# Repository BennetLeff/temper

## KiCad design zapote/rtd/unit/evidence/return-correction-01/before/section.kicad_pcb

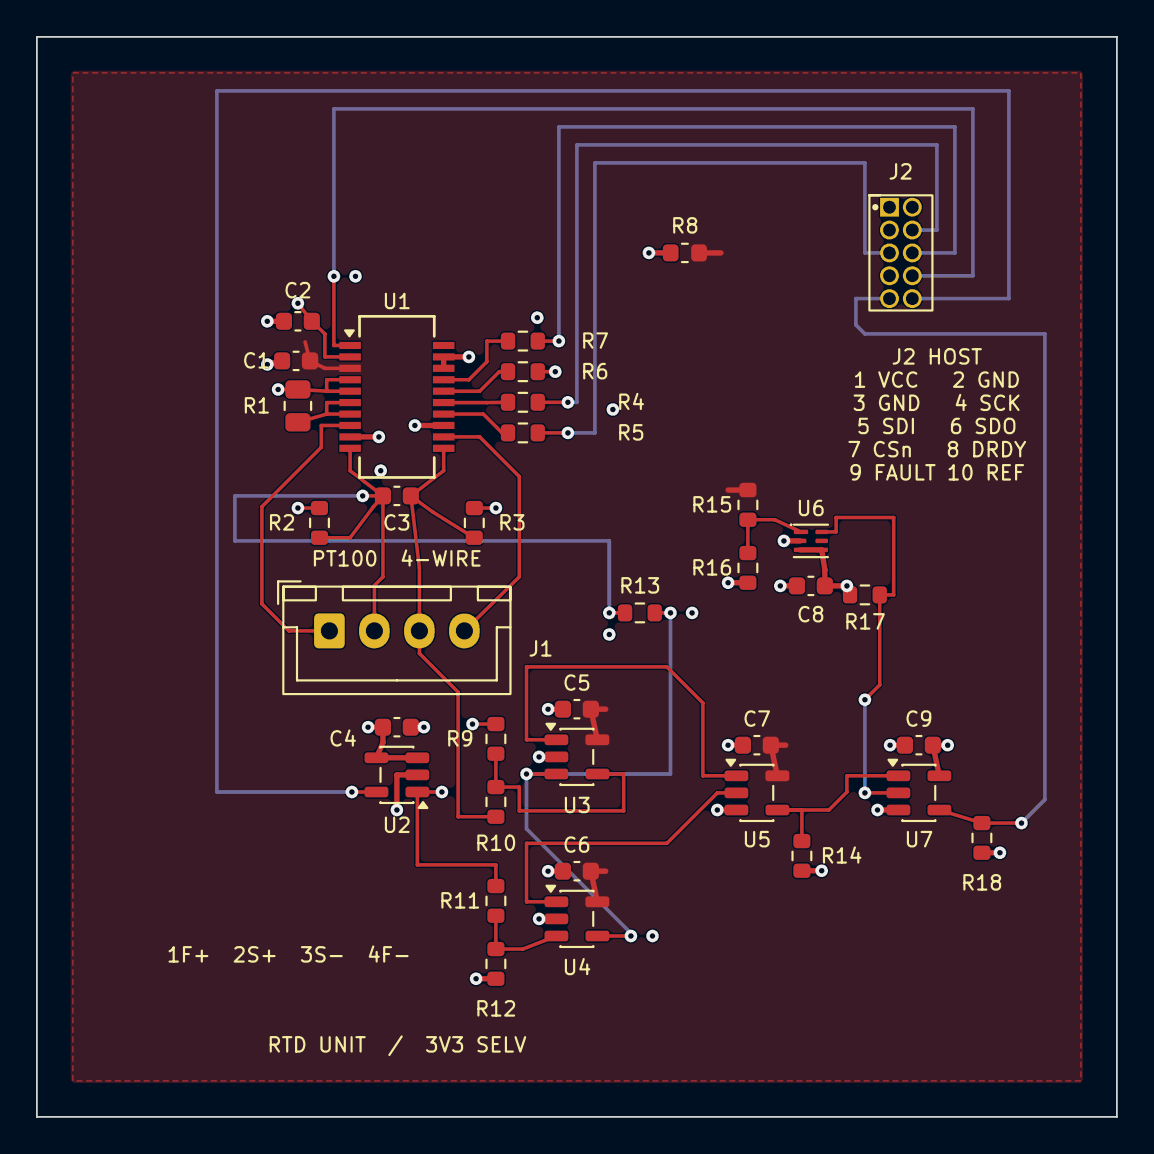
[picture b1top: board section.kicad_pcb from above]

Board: 4 copper layers, 60.0 x 60.0 mm, 36 parts (0 on the bottom side), 29 nets.

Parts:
C1, C2, C4, C5, C6, C7, C8, C9: C0603C104K5RACTU; C_0603_1608Metric
C3: C0603C102J5GACTU; C_0603_1608Metric
J1: B4B-XH-A(LF)(SN); JST_XH_B4B-XH-A_1x04_P2.50mm_Vertical
J2: FTSH-105-01-F-D; FTSH-105-01-F-D_2x5_P1.27mm
R1: RG2012V-431-W-T1; R_0805_2012Metric
R2, R3: RC0603JR-071ML; R_0603_1608Metric
R4, R5, R6, R7: RC0603FR-0733RL; R_0603_1608Metric
R8: BLM18AG121SN1D; L_0603_1608Metric
R9: ERA-3AEB6192V; R_0603_1608Metric
R10, R12, R16: ERA-3AEB103V; R_0603_1608Metric
R11: ERA-3AEB5901V; R_0603_1608Metric
R13, R14: RC0603FR-07100KL; R_0603_1608Metric
R15: ERA-3AEB1652V; R_0603_1608Metric
R17, R18: RC0603FR-0710KL; R_0603_1608Metric
U1: MAX31865AAP+; SSOP-20_3.9x8.7mm_P0.635mm
U2: REF2025AIDDCR; SOT-23-5
U3, U4: TLV3201AIDBVR; SOT-23-5
U5: SN74LVC1G08DBVR; SOT-23-5
U6: TPS389001DSER; TPS389001DSER_WSON-6_DSE
U7: SN74LVC1G38DBVR; SOT-23-5

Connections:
+3V3: C2.1, C4.1, C8.1, C9.1, J2.1, R8.1, R17.1, R18.1, U1.2, U2.3, U2.4, U6.3, U6.4, U7.5
RTD_AVDD: C1.1, C5.1, C6.1, C7.1, R8.2, R15.1, U1.3, U3.5, U4.5, U5.5
RTD_CS_N: J2.7, R6.1
RTD_DRDY: J2.8, U1.1
RTD_HW_FAULT: J2.9, R18.2, U7.4
RTD_SCK: J2.4, R4.1
RTD_SDI: J2.5, R5.1
RTD_SDO: J2.6, R7.2
SHARED_REF_2V5: J2.10, U2.5
bias: R1.1, R2.2, R3.2, U1.4, U1.5
cs_n: R6.2, U1.16
gnd: C1.2, C2.2, C4.2, C5.2, C6.2, C7.2, C8.2, C9.2, J2.2, J2.3, R12.2, R14.2, R16.2, U1.9, U1.13, U1.18, U1.19, U2.2, U3.2, U4.2, U5.3, U6.2, U7.3
inn: R9.2, R10.1, U3.4
inp: R11.2, R12.1, U4.3
refin_n: R1.2, U1.6, U1.7
reset: R17.2, U6.6, U7.2
rtd_force_n: J1.4, U1.12
rtd_force_p: J1.1, U1.8
rtd_pan.high_window-out: U4.1, U5.2
rtd_pan.low_window-out: U3.1, U5.1
rtd_sense_n: C3.2, J1.3, R3.1, R10.2, U1.11
rtd_sense_p: C3.1, J1.2, R2.1, R13.1, U1.10
sclk: R4.2, U1.15
sdi: R5.2, U1.14
sdo: R7.1, U1.17
sense: R15.2, R16.1, U6.1
vbias: R9.1, R11.1, U2.1
window_rtdin_p: R13.2, U3.3, U4.4
y: R14.1, U5.4, U7.1
